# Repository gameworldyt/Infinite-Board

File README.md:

# Infinite-Board
A Project for Hack Club HackPad. This is a the Infinite Boards Repo for me to use for daily and gameing. I am also using this project to learn coding and new skills. Also  Thanks to Hack Club for giving me this opurtunity.

**What Is the Infinite Pad?** 
Infinite Pad is a project I have been working on to submit to hack club hack pad mission. This pad can be used for gaming or work use as it has a lot of functions.

**How many keys?**
There are 12 keys with different fetures on each one. 

**What does it use?**
It uses 
Part,Quantity,Used For
XIAO RP2040,1,Microcontroller
1N4148 through-hole diode,12,Key matrix
MX-style mechanical switch,12,Keys
2-pin rotary encoder,0,Not used
0.91-inch OLED display,1,Startup display
DSA keycap,12,Keycaps
SK6812 MINI-E,0,Not used
M3 x 16mm screw,4,Case assembly
M3 x 5 x 4mm heat-set insert,4,Case screw mounting
3D printed case,1,Enclosure
PCB,1,Custom 2-layer PCB

**What is the OLED for?**
It is used for displaying text. Also It displays if the Pad is redy to be used and if it is working.

**Why you wanted a macro pad**
I wanted to make a macro pad because I would like to learn new skills and make hardware.

**Why you designed your own instead of using an existing one**
Because I wanted to learn new skills and not copy others. 

**What makes your design different/useful** 
It is also easy to use and easy for the hand to tap each button.

| Key | Function               |
| --- | ---------------------- |
| 1   | Ctrl + Windows + Right |
| 2   | R                      |
| 3   | Mute / Unmute          |
| 4   | T                      |
| 5   | Open File Explorer     |
| 6   | Windows Key            |
| 7   | Enter                  |
| 8   | 8                      |
| 9   | 9                      |
| 10  | Close current window   |
| 11  | Alt + Tab              |
| 12  | E                      |

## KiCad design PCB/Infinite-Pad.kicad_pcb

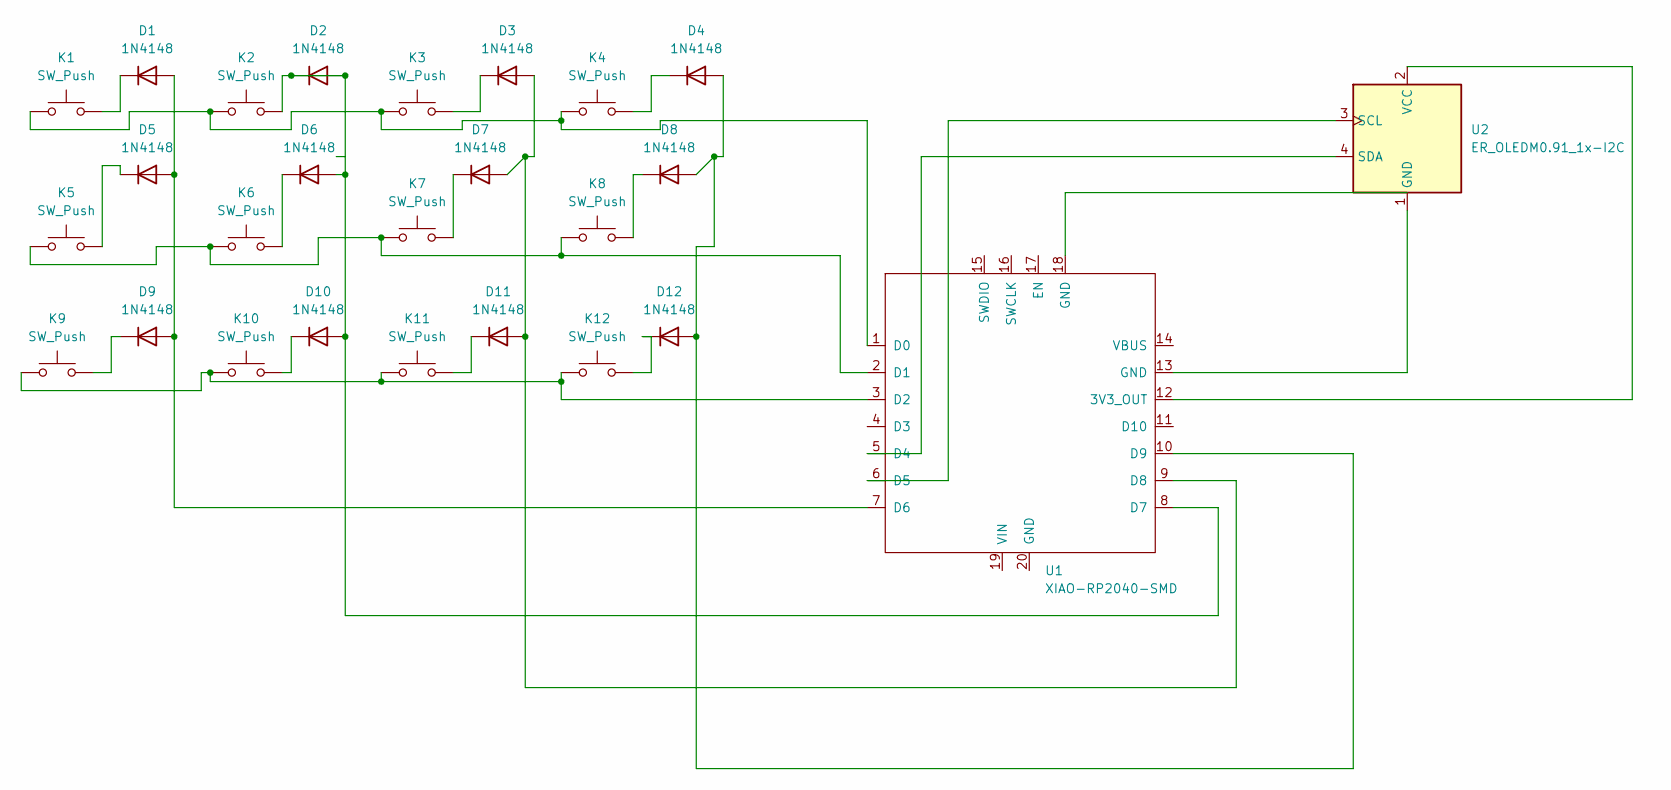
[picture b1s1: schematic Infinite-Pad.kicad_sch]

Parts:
D1, D2, D3, D4, D5, D6, D7, D8, D9, D10, D11, D12: 1N4148; D_DO-35_SOD27_P7.62mm_Horizontal
K1, K2, K3, K4, K5, K6, K7, K8, K9, K10, K11, K12: SW_Push; Nidec_Copal_CAS-120A
U1: XIAO-RP2040-SMD
U2: ER_OLEDM0.91_1x-I2C

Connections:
unnamed: D1.2 (A), D5.2 (A), D9.2 (A), U1.7 (D6)
unnamed: D1.1 (K), K1.2
unnamed: D3.1 (K), K3.2
unnamed: D4.1 (K), K4.2
unnamed: D5.1 (K), K5.2
unnamed: D6.1 (K), K6.2
unnamed: D7.1 (K), K7.2
unnamed: D8.1 (K), K8.2
unnamed: D9.1 (K), K9.2
unnamed: D2.1 (K), D2.2 (A), D6.2 (A), D10.2 (A), K2.2, U1.8 (D7)
unnamed: D10.1 (K), K10.2
unnamed: D3.2 (A), D7.2 (A), D11.2 (A), U1.9 (D8)
unnamed: D11.1 (K), K11.2
unnamed: D4.2 (A), D8.2 (A), D12.2 (A), U1.10 (D9)
unnamed: D12.1 (K), K12.2
unnamed: U1.12 (3V3_OUT), U2.2 (VCC)
unnamed: K1.1, K2.1, K3.1, K4.1, U1.1 (D0)
unnamed: K5.1, K6.1, K7.1, K8.1, U1.2 (D1)
unnamed: K9.1, K10.1, K11.1, K12.1, U1.3 (D2)
unnamed: U1.5 (D4), U2.4 (SDA)
unnamed: U1.6 (D5), U2.3 (SCL)
unnamed: U1.13 (GND), U2.1 (GND)

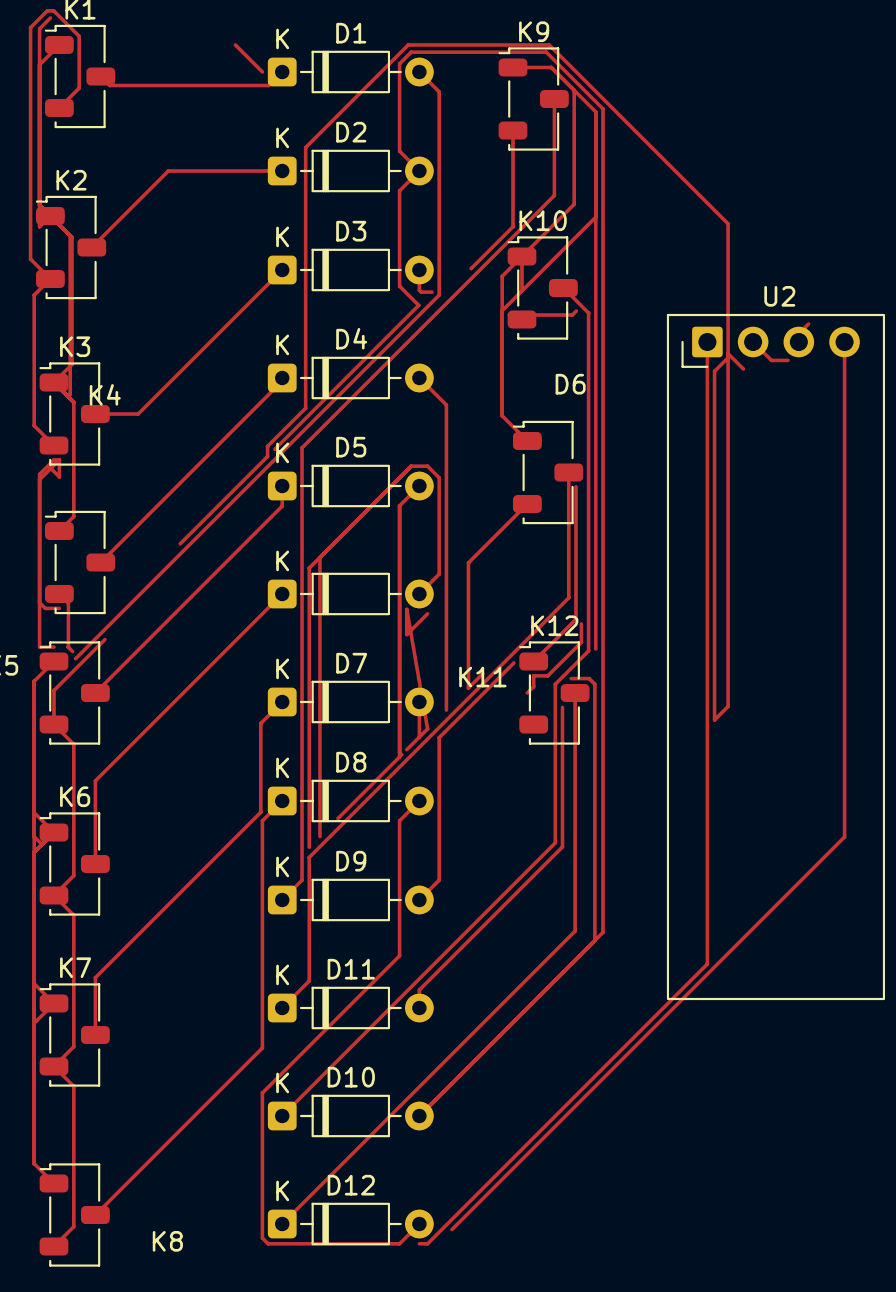
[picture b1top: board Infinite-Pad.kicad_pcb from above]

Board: 2 copper layers, 25 parts (0 on the bottom side), 18 nets.
